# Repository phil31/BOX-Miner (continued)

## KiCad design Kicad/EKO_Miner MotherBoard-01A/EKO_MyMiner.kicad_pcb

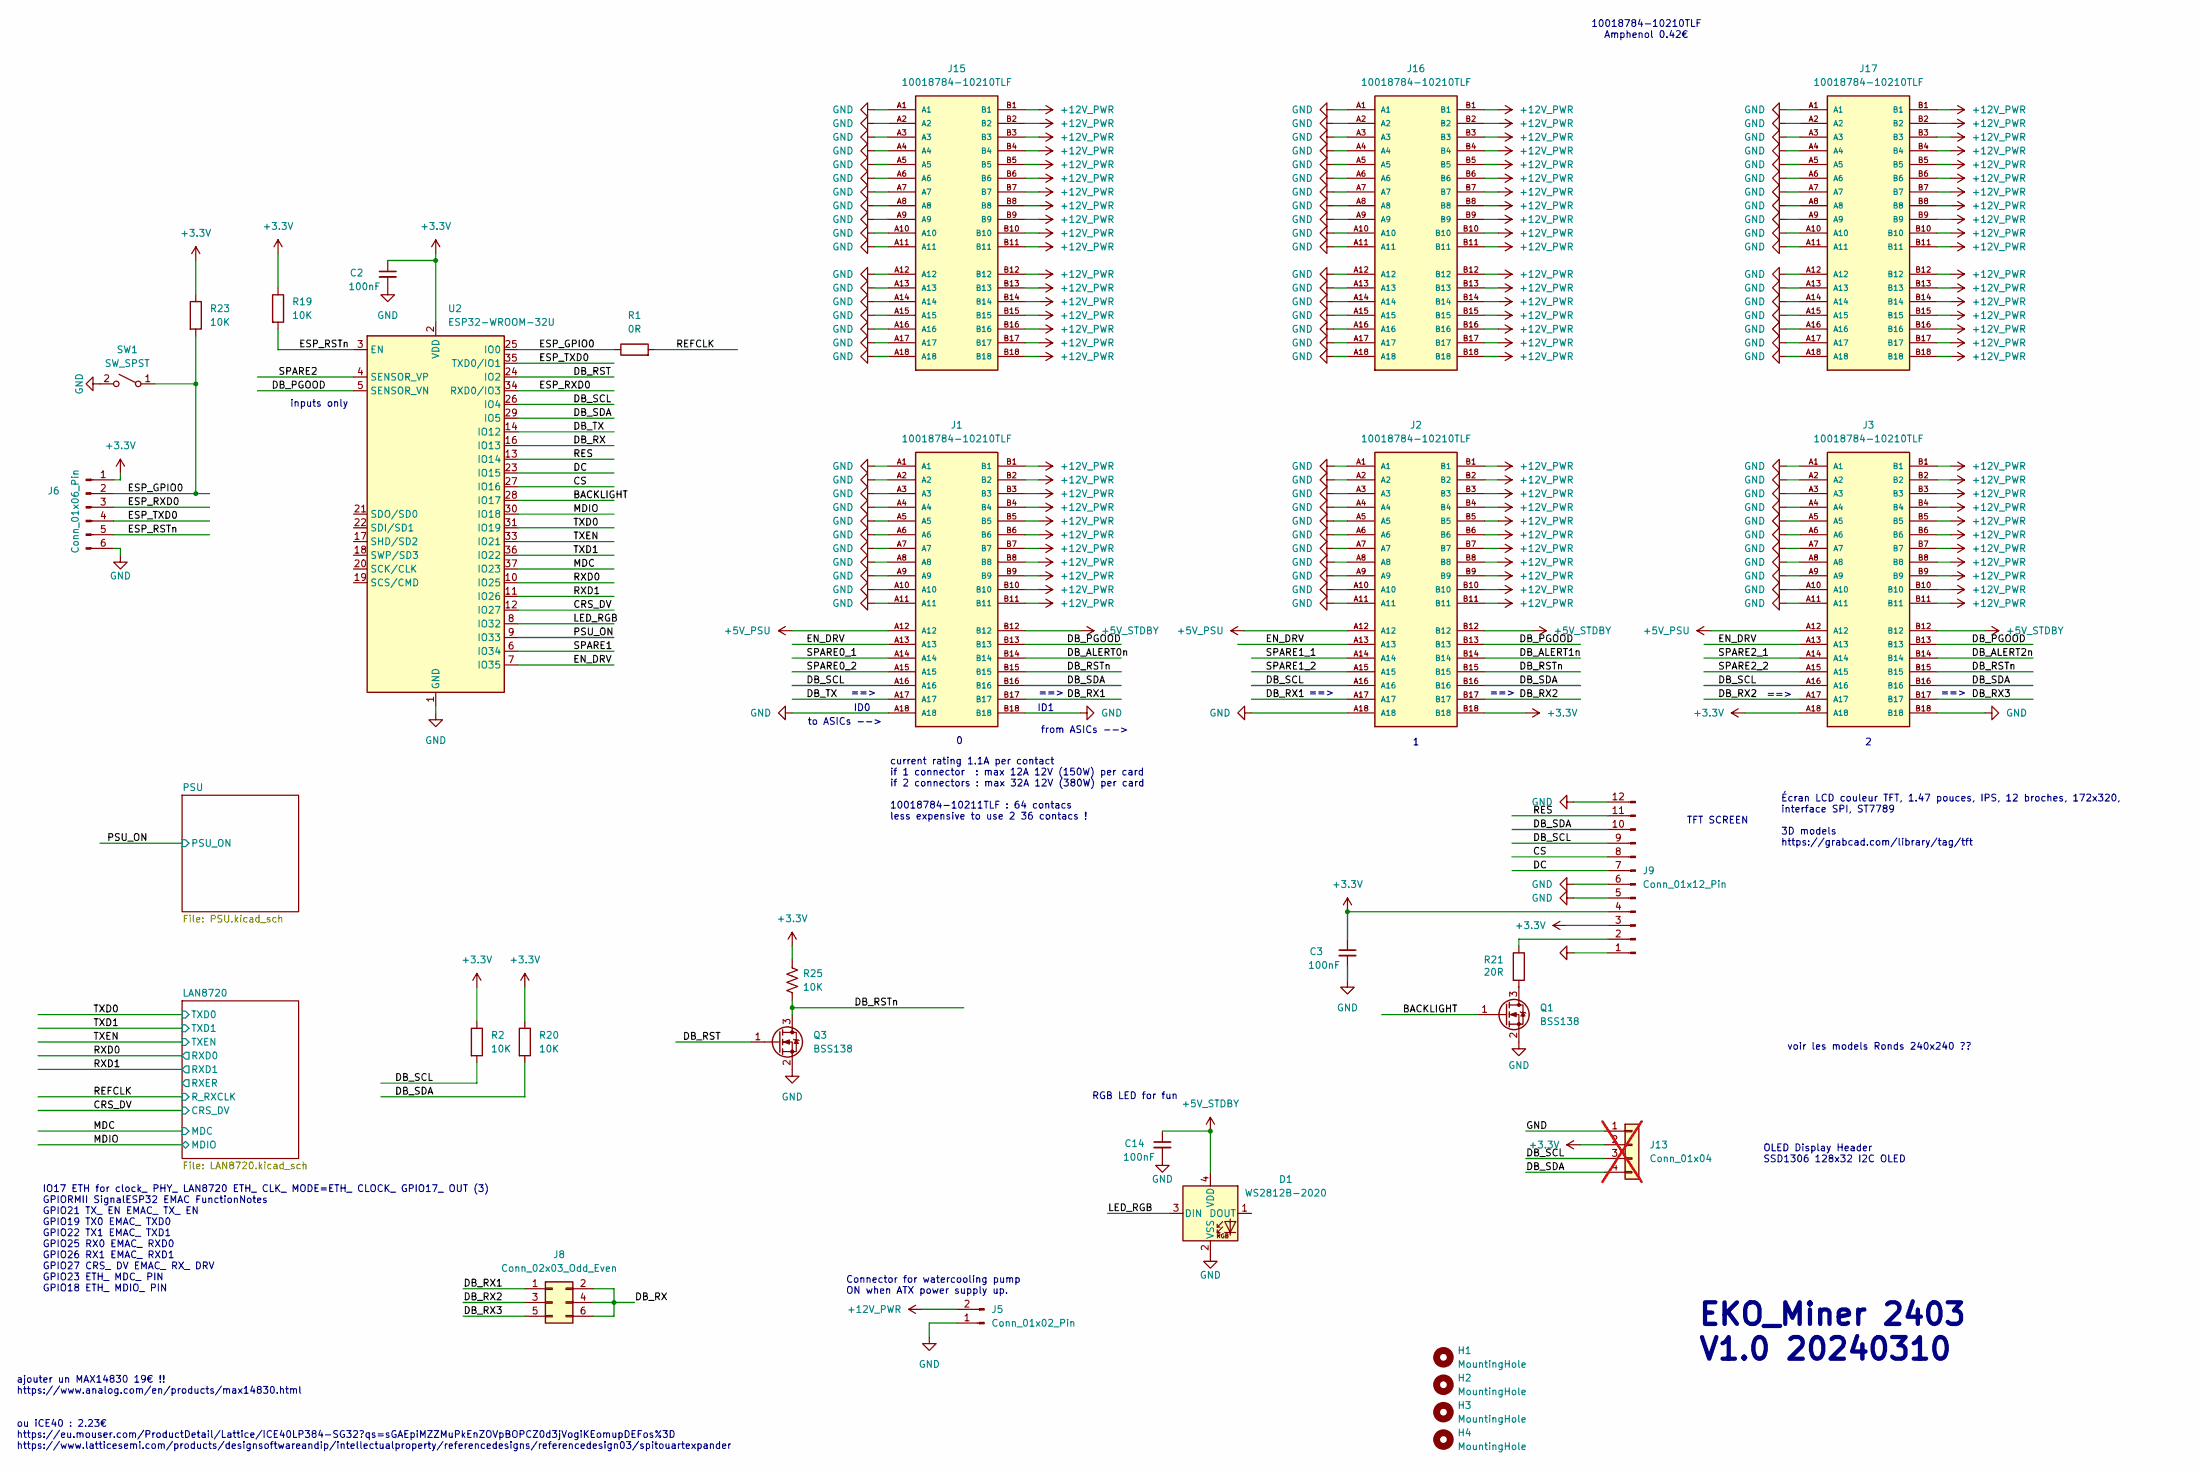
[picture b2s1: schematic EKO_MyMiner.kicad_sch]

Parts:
C2, C3, C14: 100nF; C_0603_1608Metric
D1: WS2812B-2020; WS2812B2020
H1, H2, H3, H4: MountingHole; MountingHole_3.2mm_M3_DIN965_Pad
J1, J2, J3, J15, J16, J17: 10018784-10210TLF; AMPHENOL_10018784-10210TLF; PARTREV S
J5: Conn_01x02_Pin; JST_EH_B2B-EH-A_1x02_P2.50mm_Vertical
J6: Conn_01x06_Pin; EKO_ESP_ISP
J8: Conn_02x03_Odd_Even; PinHeader_2x03_P2.54mm_Vertical
J9: Conn_01x12_Pin; LCD LBS147TC-IG01
J13: Conn_01x04; PinHeader_1x04_P2.54mm_Vertical; not fitted
Q1, Q3: BSS138; SOT-23
R1: 0R; R_0603_1608Metric
R2, R19, R20, R23: 10K; R_0603_1608Metric
R21: 20R; R_0603_1608Metric
R25: 10K; R_0402_1005Metric; PARTNO RC0402JR-0710KL
SW1: SW_SPST; SW_PUSH_6mm_H9.5mm
U2: ESP32-WROOM-32U

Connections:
+3.3V: C2.1, C3.1, J2.B18, J3.A18, J6.1, J9.3, J9.4, J13.2, R2.1, R19.1, R20.1, R23.1, R25.2, U2.2 (VDD); also elsewhere on the board
+5V_PSU: J1.A12, J2.A12, J3.A12; also elsewhere on the board
+5V_STDBY: C14.1, D1.4 (VDD), J1.B12, J2.B12, J3.B12; also elsewhere on the board
+12V_PWR: J1.B1, J1.B2, J1.B3, J1.B4, J1.B5, J1.B6, J1.B7, J1.B8, J1.B9, J1.B10, J1.B11, J2.B1, J2.B2, J2.B3, J2.B4, J2.B5, J2.B6, J2.B7, J2.B8, J2.B9, J2.B10, J2.B11, J3.B1, J3.B2, J3.B3, J3.B4, J3.B5, J3.B6, J3.B7, J3.B8, J3.B9, J3.B10, J3.B11, J5.2, J15.B1, J15.B2, J15.B3, J15.B4, J15.B5, J15.B6, J15.B7, J15.B8, J15.B9, J15.B10, J15.B11, J15.B12, J15.B13, J15.B14, J15.B15, J15.B16, J15.B17, J15.B18, J16.B1, J16.B2, J16.B3, J16.B4, J16.B5, J16.B6, J16.B7, J16.B8, J16.B9, J16.B10, J16.B11, J16.B12, J16.B13, J16.B14, J16.B15, J16.B16, J16.B17, J16.B18, J17.B1, J17.B2, J17.B3, J17.B4, J17.B5, J17.B6, J17.B7, J17.B8, J17.B9, J17.B10, J17.B11, J17.B12, J17.B13, J17.B14, J17.B15, J17.B16, J17.B17, J17.B18; also elsewhere on the board
/BACKLIGHT: Q1.1 (G), U2.28 (IO17)
/CRS_DV: U2.12 (IO27); also elsewhere on the board
/CS: J9.8, U2.27 (IO16)
/DB_ALERT0n: J1.B14
/DB_ALERT1n: J2.B14
/DB_ALERT2n: J3.B14
/DB_PGOOD: J1.B13, J2.B13, J3.B13, U2.5 (SENSOR_VN)
/DB_RST: Q3.1 (G), U2.24 (IO2)
/DB_RSTn: J1.B15, J2.B15, J3.B15, Q3.3 (D), R25.1
/DB_RX: J8.2, J8.4, J8.6, U2.16 (IO13)
/DB_RX1: J1.B17, J2.A17, J8.1
/DB_RX2: J2.B17, J3.A17, J8.3
/DB_RX3: J3.B17, J8.5
/DB_SCL: J1.A16, J2.A16, J3.A16, J9.9, J13.3, R2.2, U2.26 (IO4)
/DB_SDA: J1.B16, J2.B16, J3.B16, J9.10, J13.4, R20.2, U2.29 (IO5)
/DB_TX: J1.A17, U2.14 (IO12)
/DC: J9.7, U2.23 (IO15)
/EN_DRV: J1.A13, J2.A13, J3.A13, U2.7 (IO35)
/ESP_GPIO0: J6.2, R1.1, R23.2, SW1.1 (A), U2.25 (IO0)
/ESP_RSTn: J6.5, R19.2, U2.3 (EN)
/ESP_RXD0: J6.3, U2.34 (RXD0/IO3)
/ESP_TXD0: J6.4, U2.35 (TXD0/IO1)
/LED_RGB: D1.3 (DIN), U2.8 (IO32)
/MDC: U2.37 (IO23); also elsewhere on the board
/MDIO: U2.30 (IO18); also elsewhere on the board
/PSU_ON: U2.9 (IO33); also elsewhere on the board
/REFCLK: R1.2; also elsewhere on the board
/RES: J9.11, U2.13 (IO14)
/RXD0: U2.10 (IO25); also elsewhere on the board
/RXD1: U2.11 (IO26); also elsewhere on the board
/SPARE0_1: J1.A14
/SPARE0_2: J1.A15
/SPARE1: U2.6 (IO34)
/SPARE1_1: J2.A14
/SPARE1_2: J2.A15
/SPARE2: U2.4 (SENSOR_VP)
/SPARE2_1: J3.A14
/SPARE2_2: J3.A15
/TXD0: U2.31 (IO19); also elsewhere on the board
/TXD1: U2.36 (IO22); also elsewhere on the board
/TXEN: U2.33 (IO21); also elsewhere on the board
GND: C2.2, C3.2, C14.2, D1.2 (VSS), J1.A1, J1.A2, J1.A3, J1.A4, J1.A5, J1.A6, J1.A7, J1.A8, J1.A9, J1.A10, J1.A11, J1.A18, J1.B18, J2.A1, J2.A2, J2.A3, J2.A4, J2.A5, J2.A6, J2.A7, J2.A8, J2.A9, J2.A10, J2.A11, J2.A18, J3.A1, J3.A2, J3.A3, J3.A4, J3.A5, J3.A6, J3.A7, J3.A8, J3.A9, J3.A10, J3.A11, J3.B18, J5.1, J6.6, J9.1, J9.5, J9.6, J9.12, J13.1, J15.A1, J15.A2, J15.A3, J15.A4, J15.A5, J15.A6, J15.A7, J15.A8, J15.A9, J15.A10, J15.A11, J15.A12, J15.A13, J15.A14, J15.A15, J15.A16, J15.A17, J15.A18, J16.A1, J16.A2, J16.A3, J16.A4, J16.A5, J16.A6, J16.A7, J16.A8, J16.A9, J16.A10, J16.A11, J16.A12, J16.A13, J16.A14, J16.A15, J16.A16, J16.A17, J16.A18, J17.A1, J17.A2, J17.A3, J17.A4, J17.A5, J17.A6, J17.A7, J17.A8, J17.A9, J17.A10, J17.A11, J17.A12, J17.A13, J17.A14, J17.A15, J17.A16, J17.A17, J17.A18, Q1.2 (S), Q3.2 (S), SW1.2 (B), U2.1 (GND), U2.15 (GND), U2.38 (GND), U2.39 (GND); also elsewhere on the board
unnamed: J9.2, R21.1
unnamed: Q1.3 (D), R21.2

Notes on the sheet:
to ASICs -->
current rating 1.1A per contact if 1 connector : max 12A 12V (150W) per card if 2 connectors : max 32A 12V (380W) per card 10018784-10211TLF : 64 contacs less expensive to use 2 36 contacs !
10018784-10210TLF Amphenol 0.42€
voir les models Ronds 240x240 ??
TFT SCREEN
==>
ajouter un MAX14830 19€ !! https://www.analog.com/en/products/max14830.html ou iCE40 : 2.23€ https://eu.mouser.com/ProductDetail/Lattice/ICE40LP384-SG32?qs=sGAEpiMZZMuPkEnZOVpBOPCZ0d3jVogiKEomupDEFos%3D https://www.latticesemi.com/products/designsoftwareandip/intellectualproperty/referencedesigns/r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
OLED Display Header SSD1306 128x32 I2C OLED
Connector for watercooling pump ON when ATX power supply up.
ID0
Écran LCD couleur TFT, 1.47 pouces, IPS, 12 broches, 172x320, interface SPI, ST7789 3D models https://grabcad.com/library/tag/tft
inputs only
IO17 ETH for clock_ PHY_ LAN8720 ETH_ CLK_ MODE=ETH_ CLOCK_ GPIO17_ OUT (3) GPIORMII SignalESP32 EMAC FunctionNotes GPIO21 TX_ EN EMAC_ TX_ EN GPIO19 TX0 EMAC_ TXD0 GPIO22 TX1 EMAC_ TXD1 GPIO25 RX0 EMAC_ RXD0 GPIO26 RX1 EMAC_ RXD1 GPIO27 CRS_ DV EMAC_ RX_ DRV GPIO23 ETH_ MDC_ PIN GPIO18 ETH_ MDIO_ 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
from ASICs -->
RGB LED for fun
ID1
EKO_Miner 2403 V1.0 20240310

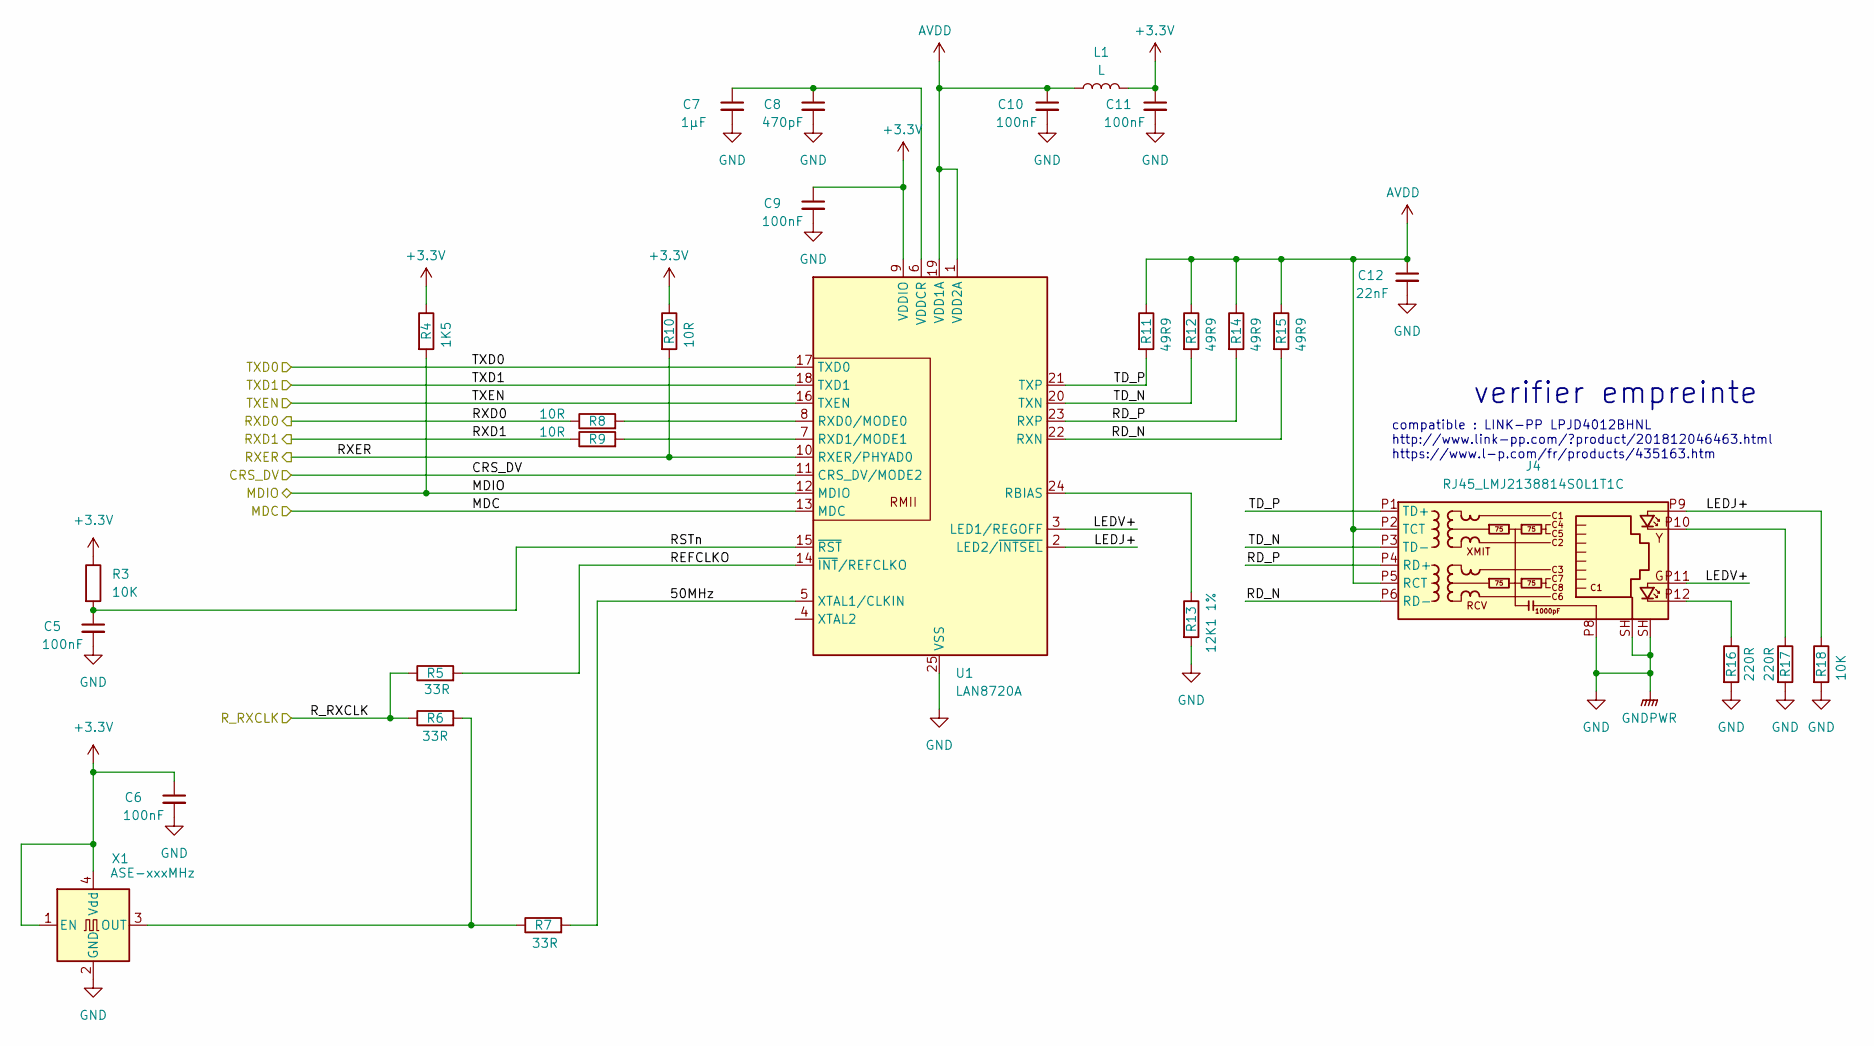
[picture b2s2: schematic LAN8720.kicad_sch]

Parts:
C5, C6, C9, C10, C11: 100nF; C_0603_1608Metric
C7: 1µF; C_0603_1608Metric
C8: 470pF; C_0603_1608Metric
C12: 22nF; C_0603_1608Metric
J4: RJ45_LMJ2138814S0L1T1C; LMJ2138814SOL1T1C
L1: L; L_0805_2012Metric
R3, R18: 10K; R_0603_1608Metric
R4: 1K5; R_0603_1608Metric
R5, R6, R7: 33R; R_0603_1608Metric
R8, R9, R10: 10R; R_0603_1608Metric
R11, R12, R14, R15: 49R9; R_0603_1608Metric
R13: 12K1 1%; R_0603_1608Metric
R16, R17: 220R; R_0603_1608Metric
U1: LAN8720A; LAN8720_VQFN-24-1EP_4x4mm_P0.5mm_EP2.5x2.5mm_ThermalVias
X1: ASE-xxxMHz; Oscillator_SMD_Abracon_ASE-4Pin_3.2x2.5mm

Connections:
+3.3V: C6.1, C9.1, C11.1, L1.2, R3.1, R4.1, R10.1, U1.9 (VDDIO), X1.1 (EN), X1.4 (Vdd); also elsewhere on the board
/CRS_DV: U1.11 (CRS_DV/MODE2); also elsewhere on the board
/LAN8720/50MHz: R7.2, U1.5 (XTAL1/CLKIN)
/LAN8720/LEDJ+: J4.P9, R18.1, U1.2 (LED2/~INTSEL)
/LAN8720/LEDV+: J4.P11, U1.3 (LED1/REGOFF)
/LAN8720/RD_N: J4.P6 (RD-), R15.2, U1.22 (RXN)
/LAN8720/RD_P: J4.P4 (RD+), R14.2, U1.23 (RXP)
/LAN8720/REFCLKO: R5.2, U1.14 (~INT/REFCLKO)
/LAN8720/RSTn: C5.1, R3.2, U1.15 (~RST)
/LAN8720/RXER: R10.2, U1.10 (RXER/PHYAD0)
/LAN8720/TD_N: J4.P3 (TD-), R12.2, U1.20 (TXN)
/LAN8720/TD_P: J4.P1 (TD+), R11.2, U1.21 (TXP)
/MDC: U1.13 (MDC); also elsewhere on the board
/MDIO: R4.2, U1.12 (MDIO); also elsewhere on the board
/REFCLK: R5.1, R6.1; also elsewhere on the board
/RXD0: R8.1; also elsewhere on the board
/RXD1: R9.1; also elsewhere on the board
/TXD0: U1.17 (TXD0); also elsewhere on the board
/TXD1: U1.18 (TXD1); also elsewhere on the board
/TXEN: U1.16 (TXEN); also elsewhere on the board
AVDD: C10.1, C12.1, J4.P2 (TCT), J4.P5 (RCT), L1.1, R11.1, R12.1, R14.1, R15.1, U1.1 (VDD2A), U1.19 (VDD1A)
GND: C5.2, C6.2, C7.2, C8.2, C9.2, C10.2, C11.2, C12.2, J4.P8, J4.SH, R13.2, R16.2, R17.2, R18.2, U1.25 (VSS), X1.2 (GND); also elsewhere on the board
unnamed: J4.P10, R17.1
unnamed: J4.P12, R16.1
unnamed: R13.1, U1.24 (RBIAS)
unnamed: R8.2, U1.8 (RXD0/MODE0)
unnamed: R9.2, U1.7 (RXD1/MODE1)
unnamed: C7.1, C8.1, U1.6 (VDDCR)
unnamed: R6.2, R7.1, X1.3 (OUT)

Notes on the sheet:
compatible : LINK-PP LPJD4012BHNL http://www.link-pp.com/?product/201812046463.html https://www.l-p.com/fr/products/435163.htm
verifier empreinte

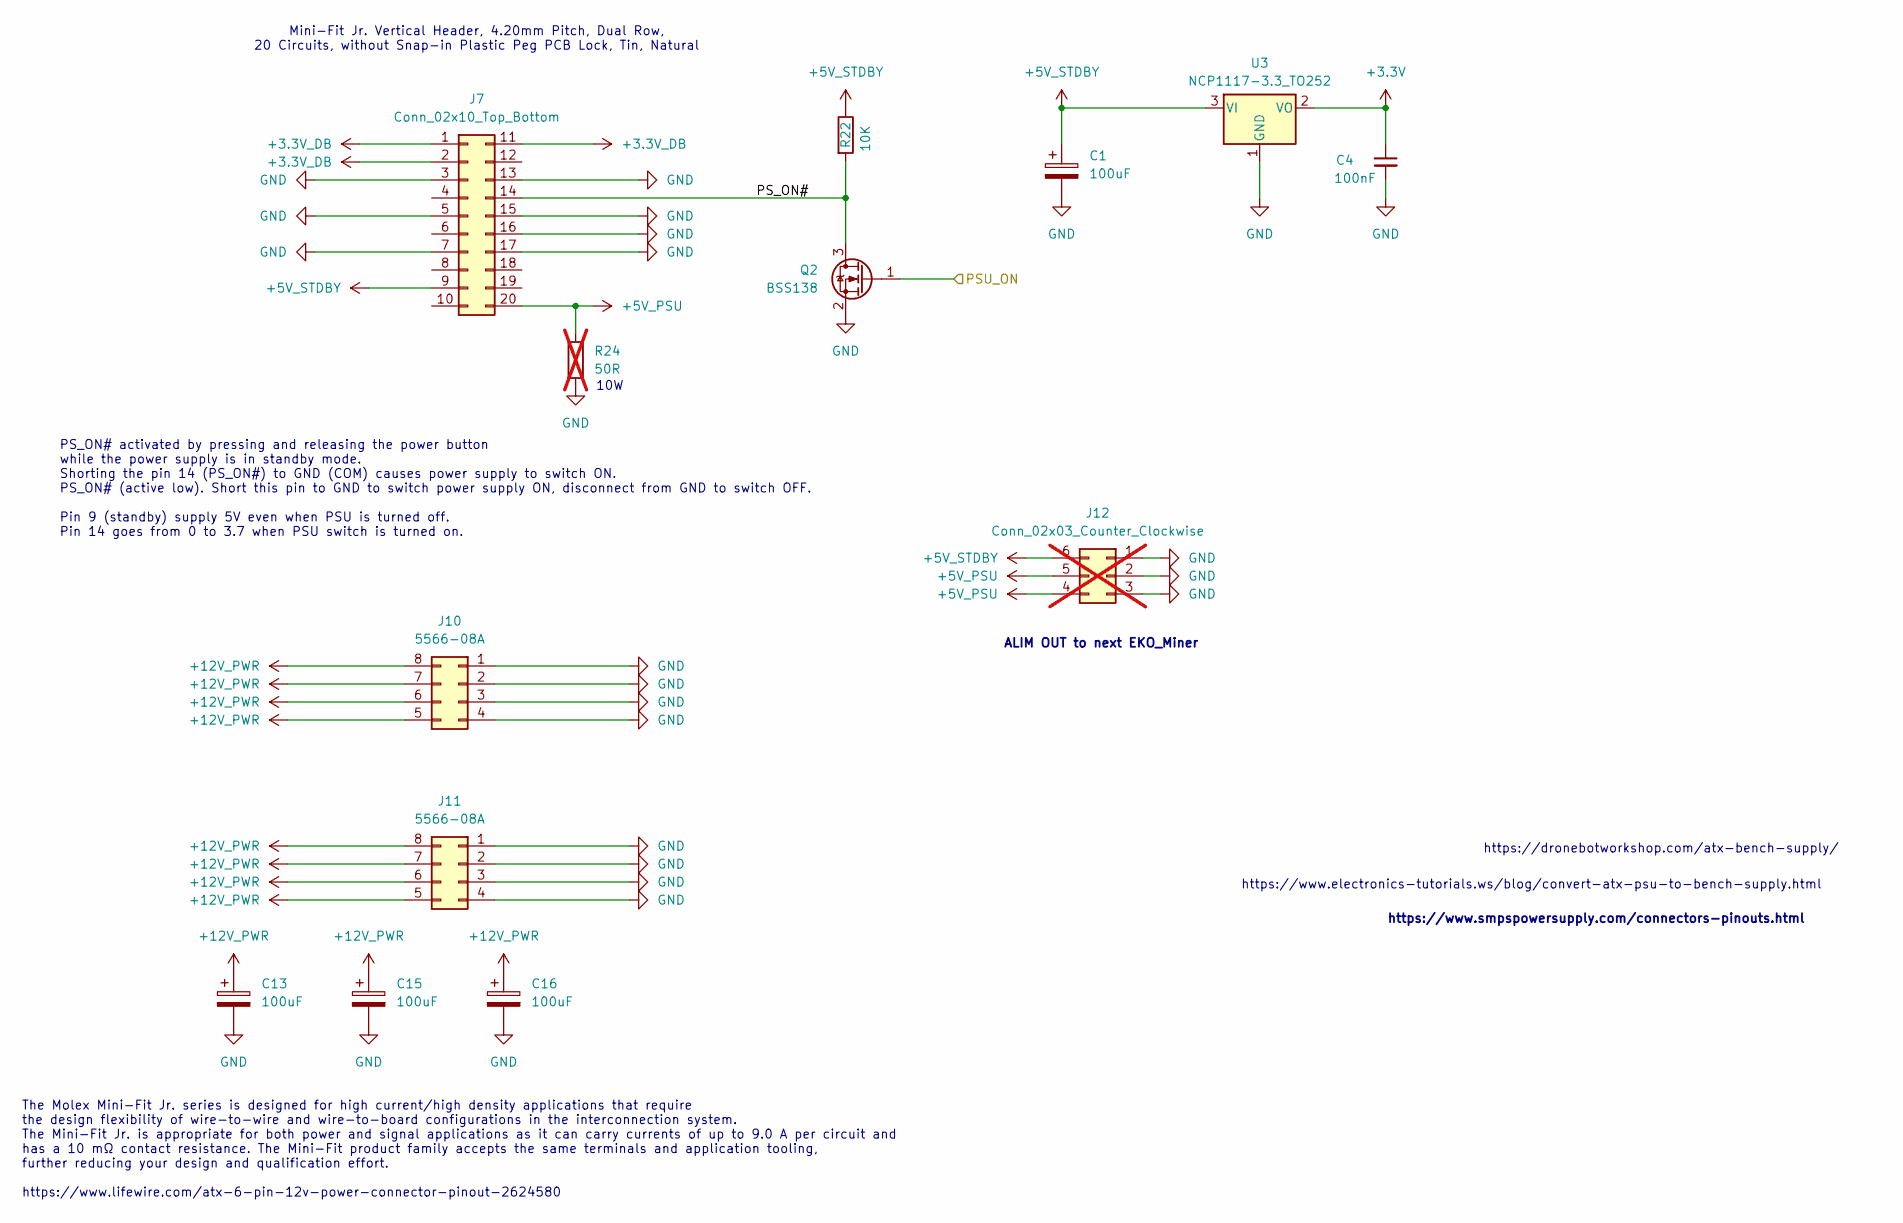
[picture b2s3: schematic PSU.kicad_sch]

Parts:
C1, C13, C15, C16: 100uF; CP_Elec_5x5.7
C4: 100nF; C_0603_1608Metric
J7: Conn_02x10_Top_Bottom; Molex_Mini-Fit_Jr_5566-20A_2x10_P4.20mm_Vertical
J10, J11: 5566-08A; Molex_Mini-Fit_Jr_5566-08A2_2x04_P4.20mm_Vertical
J12: Conn_02x03_Counter_Clockwise; Molex_Mini-Fit_Jr_5566-06A2_2x03_P4.20mm_Vertical; not fitted
Q2: BSS138; SOT-23
R22: 10K; R_0603_1608Metric
R24: 50R; R_Axial_Power_L25.0mm_W6.4mm_P27.94mm; not fitted
U3: NCP1117-3.3_TO252; TO-252-2

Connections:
+3.3V: C4.1, U3.2 (VO); also elsewhere on the board
+3.3V_DB: J7.1, J7.2, J7.11
+5V_PSU: J7.20, J12.4, J12.5, R24.1; also elsewhere on the board
+5V_STDBY: C1.1, J7.9, J12.6, R22.1, U3.3 (VI); also elsewhere on the board
+12V_PWR: C13.1, C15.1, C16.1, J10.5, J10.6, J10.7, J10.8, J11.5, J11.6, J11.7, J11.8; also elsewhere on the board
/PSU/PS_ON#: J7.14, Q2.3 (D), R22.2
/PSU_ON: Q2.1 (G); also elsewhere on the board
GND: C1.2, C4.2, C13.2, C15.2, C16.2, J7.3, J7.5, J7.7, J7.13, J7.15, J7.16, J7.17, J10.1, J10.2, J10.3, J10.4, J11.1, J11.2, J11.3, J11.4, J12.1, J12.2, J12.3, Q2.2 (S), R24.2, U3.1 (GND); also elsewhere on the board

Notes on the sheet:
The Molex Mini-Fit Jr. series is designed for high current/high density applications that require the design flexibility of wire-to-wire and wire-to-board configurations in the interconnection system. The Mini-Fit Jr. is appropriate for both power and signal applications as it can carry currents of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
https://www.smpspowersupply.com/connectors-pinouts.html
https://dronebotworkshop.com/atx-bench-supply/
Mini-Fit Jr. Vertical Header, 4.20mm Pitch, Dual Row, 20 Circuits, without Snap-in Plastic Peg PCB Lock, Tin, Natural
PS_ON# activated by pressing and releasing the power button while the power supply is in standby mode. Shorting the pin 14 (PS_ON#) to GND (COM) causes power supply to switch ON. PS_ON# (active low). Short this pin to GND to switch power supply ON, disconnect from GND to switch OFF. Pin 9 (standby)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
https://www.electronics-tutorials.ws/blog/convert-atx-psu-to-bench-supply.html
10W
ALIM OUT to next EKO_Miner

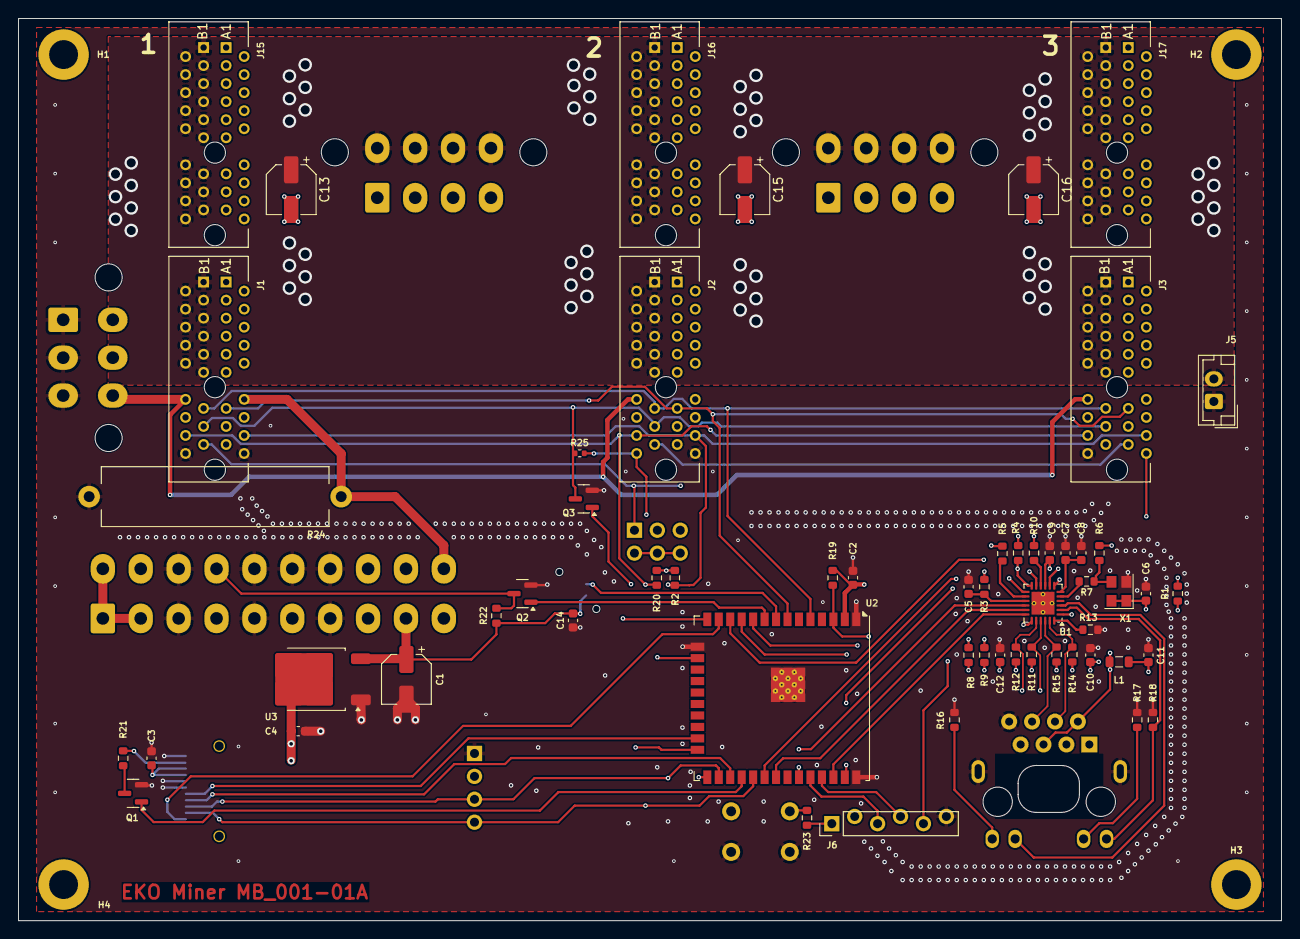
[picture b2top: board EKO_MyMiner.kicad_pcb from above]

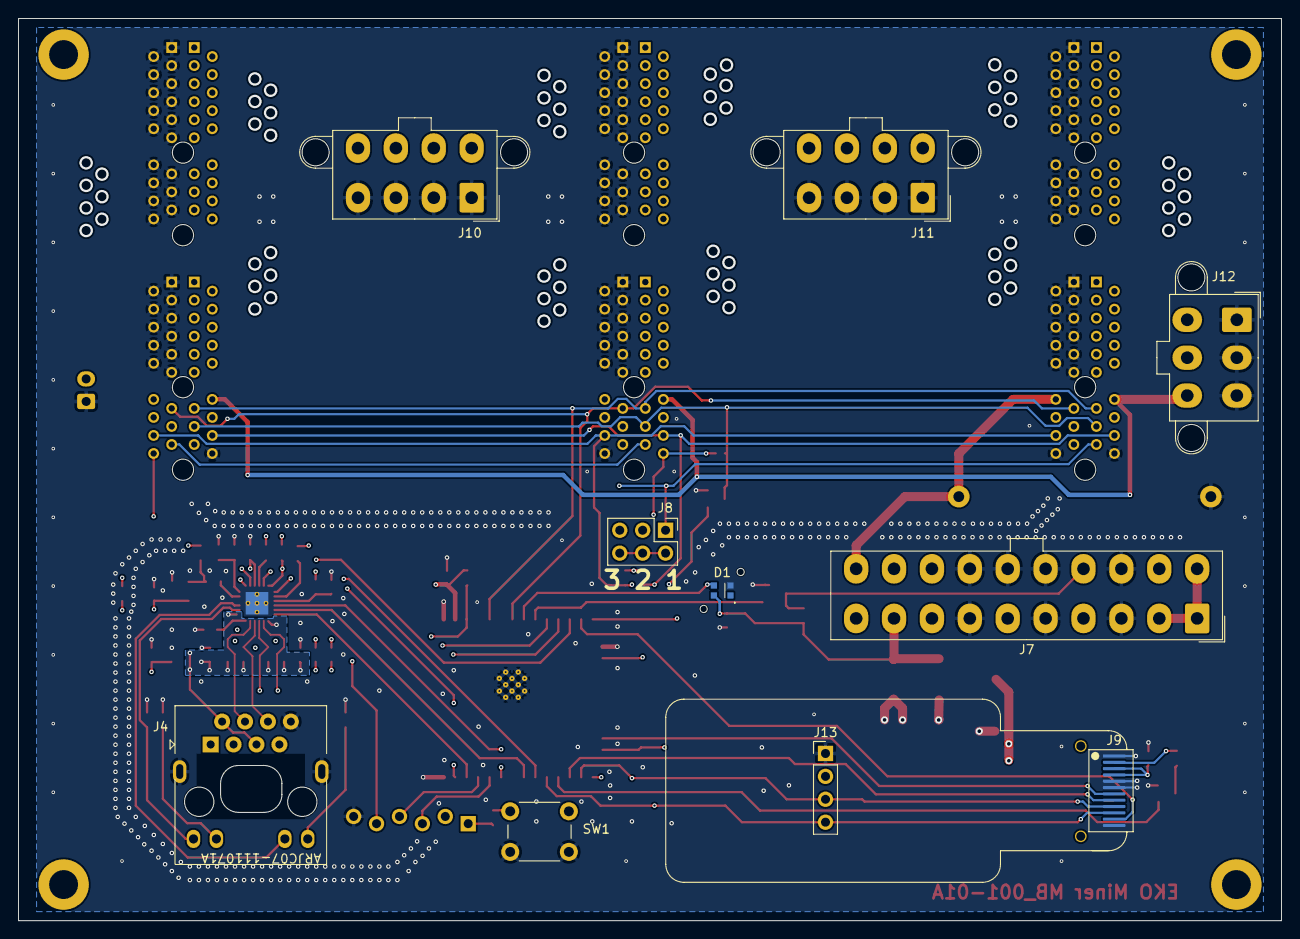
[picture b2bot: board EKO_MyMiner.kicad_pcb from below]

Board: 4 copper layers, 140.0 x 100.0 mm, 71 parts (10 on the bottom side), 57 nets.

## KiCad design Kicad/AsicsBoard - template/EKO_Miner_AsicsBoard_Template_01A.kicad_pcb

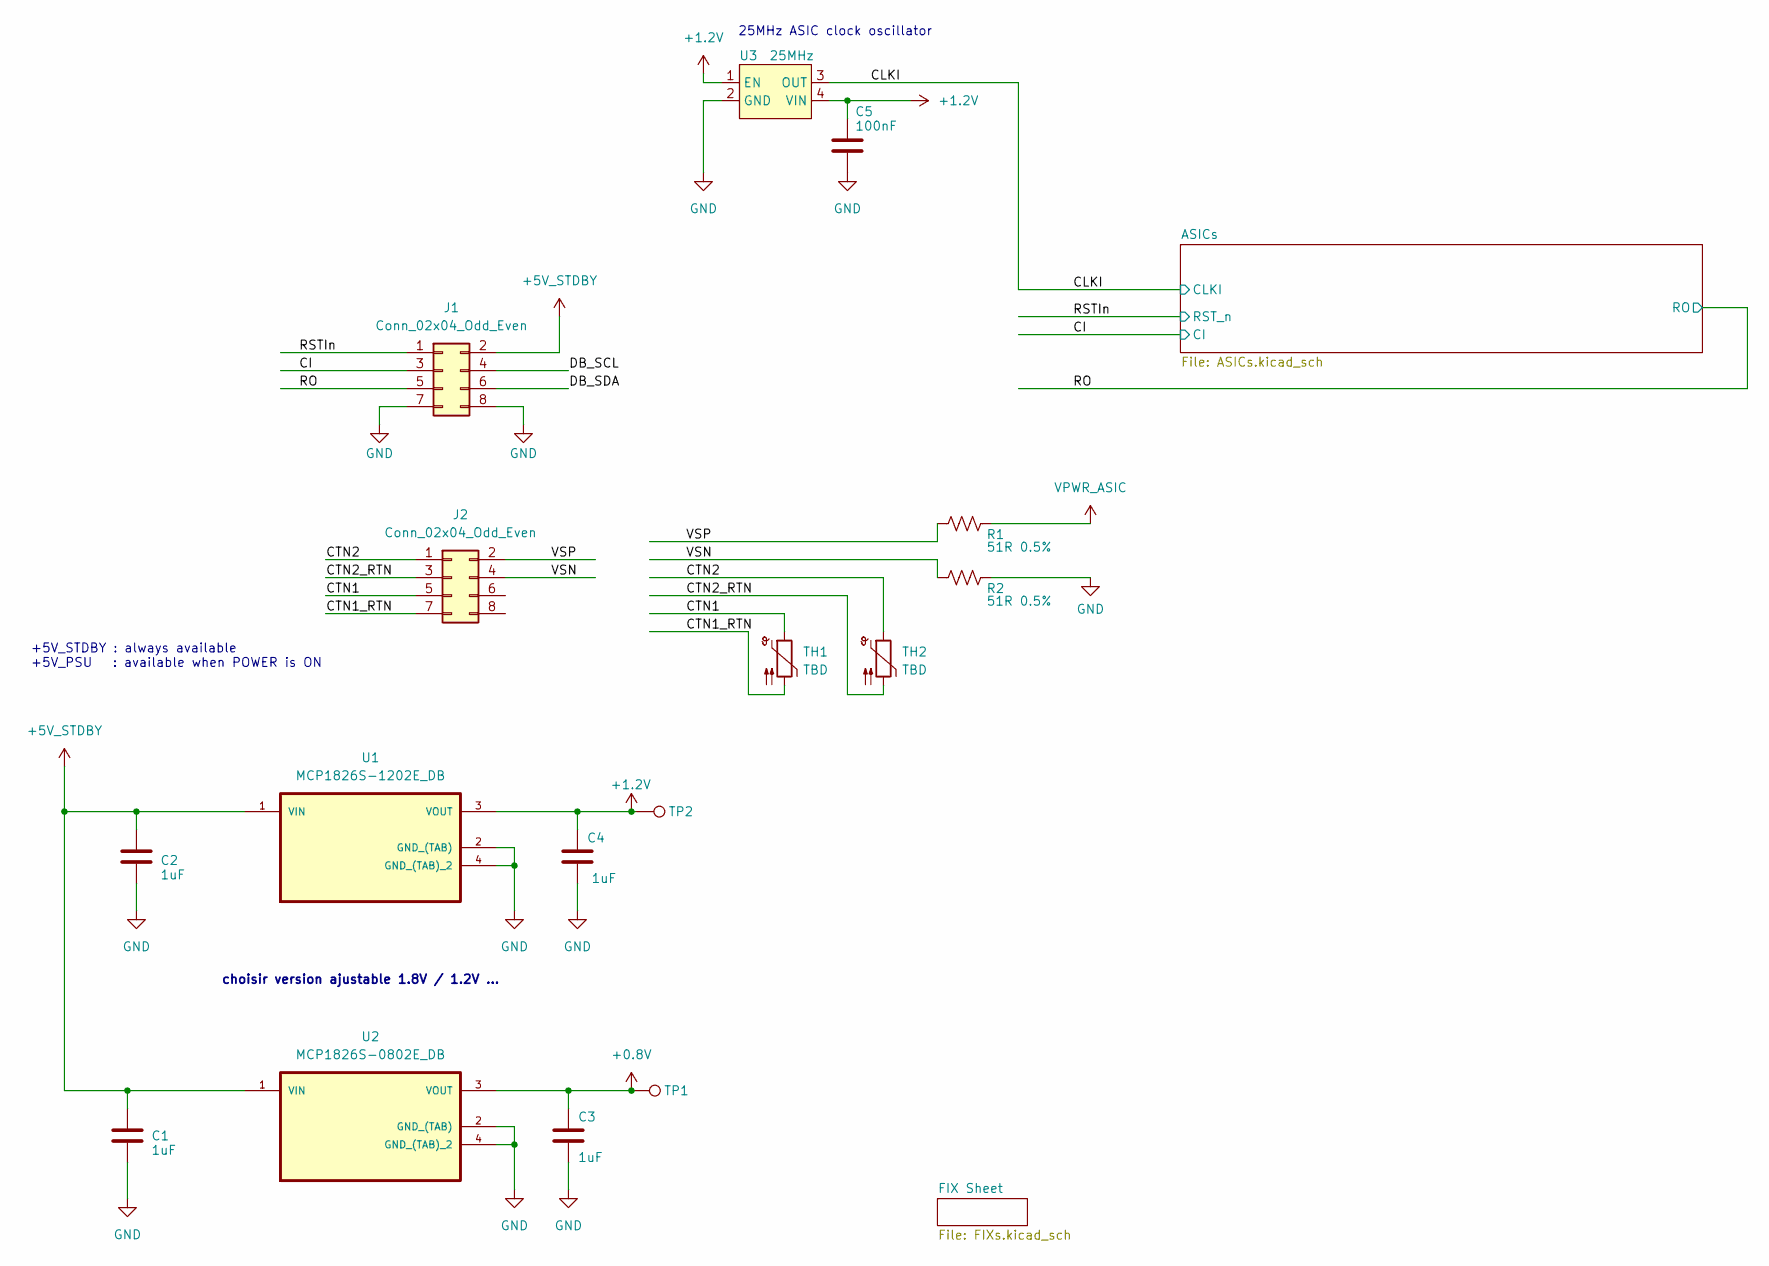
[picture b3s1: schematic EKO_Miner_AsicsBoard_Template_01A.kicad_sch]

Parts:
C1, C2, C3, C4: 1uF; C_0805_2012Metric_Pad1.18x1.45mm_HandSolder
C5: 100nF; C_0805_2012Metric_Pad1.18x1.45mm_HandSolder
J1, J2: Conn_02x04_Odd_Even; PinHeader_2x04_P2.54mm_Vertical_SMD
R1, R2: 51R 0.5%; R_0805_2012Metric_Pad1.20x1.40mm_HandSolder
TH1, TH2: TBD; R_1206_3216Metric_Pad1.30x1.75mm_HandSolder
TP1, TP2: TestPoint; TestPoint_Pad_D1.0mm
U1: MCP1826S-1202E_DB; MCP1826S
U2: MCP1826S-0802E_DB; MCP1826S
U3: 25MHz; Oscillator_SMD_Abracon_ASE-4Pin_3.2x2.5mm

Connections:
+0.8V: C3.1, TP1.1, U2.3 (VOUT)
+1.2V: C4.1, C5.1, TP2.1, U1.3 (VOUT), U3.1 (EN), U3.4 (VIN)
+5V_STDBY: C1.1, C2.1, J1.2, U1.1 (VIN), U2.1 (VIN)
/CI: J1.3; also elsewhere on the board
/CLKI: U3.3 (OUT); also elsewhere on the board
/CTN1: J2.5, TH1.1
/CTN1_RTN: J2.7, TH1.2
/CTN2: J2.1, TH2.1
/CTN2_RTN: J2.3, TH2.2
/DB_SCL: J1.4
/DB_SDA: J1.6
/RO: J1.5; also elsewhere on the board
/RSTIn: J1.1; also elsewhere on the board
/VSN: J2.4, R2.2
/VSP: J2.2, R1.2
GND: C1.2, C2.2, C3.2, C4.2, C5.2, J1.7, J1.8, R2.1, U1.2 (GND_(TAB)), U1.4 (GND_(TAB)_2), U2.2 (GND_(TAB)), U2.4 (GND_(TAB)_2), U3.2 (GND); also elsewhere on the board
VPWR_ASIC: R1.1; also elsewhere on the board

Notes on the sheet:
+5V_STDBY : always available +5V_PSU : available when POWER is ON
25MHz ASIC clock oscillator
choisir version ajustable 1.8V / 1.2V ...

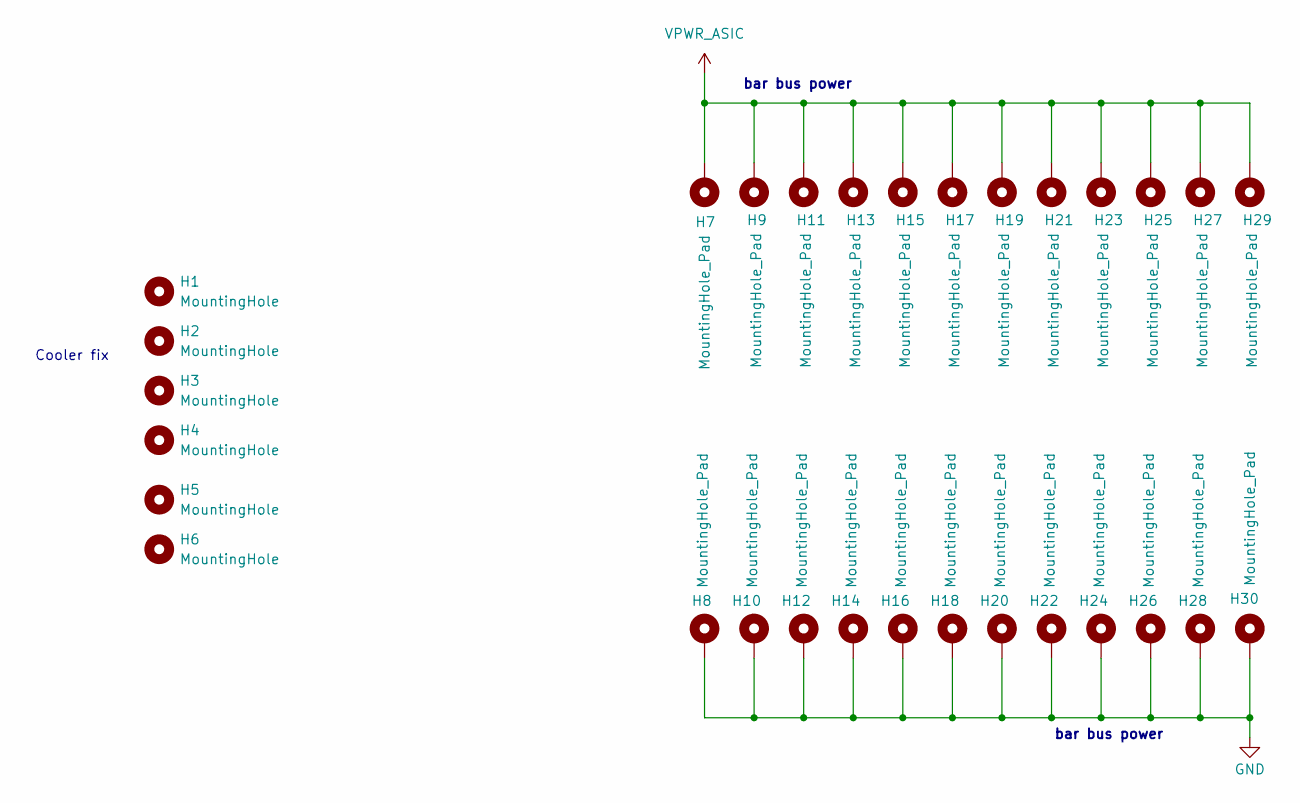
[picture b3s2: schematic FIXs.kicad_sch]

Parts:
H1, H2, H3, H4, H5, H6: MountingHole; MountingHole_3.2mm_M3_ISO7380
H7, H8, H9, H10, H11, H12, H13, H14, H15, H16, H17, H18, H19, H20, H21, H22, H23, H24, H25, H26, H27, H28, H29, H30: MountingHole_Pad; SMTSO-M3-3ET

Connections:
GND: H8.1, H10.1, H12.1, H14.1, H16.1, H18.1, H20.1, H22.1, H24.1, H26.1, H28.1, H30.1; also elsewhere on the board
VPWR_ASIC: H7.1, H9.1, H11.1, H13.1, H15.1, H17.1, H19.1, H21.1, H23.1, H25.1, H27.1, H29.1; also elsewhere on the board

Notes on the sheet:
Cooler fix
bar bus power

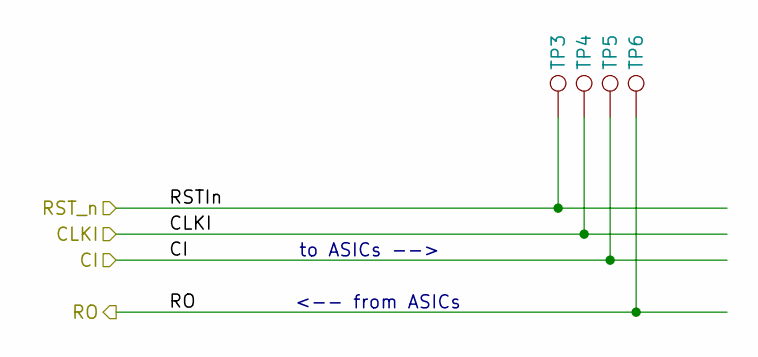
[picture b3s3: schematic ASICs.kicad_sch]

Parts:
TP3, TP4, TP5, TP6: TestPoint; TestPoint_Pad_D1.0mm

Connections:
/CI: TP5.1; also elsewhere on the board
/CLKI: TP4.1; also elsewhere on the board
/RO: TP6.1; also elsewhere on the board
/RSTIn: TP3.1; also elsewhere on the board

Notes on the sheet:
<-- from ASICs
to ASICs -->

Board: 6 copper layers, 50 parts (42 on the bottom side), 15 nets, no tracks yet.
